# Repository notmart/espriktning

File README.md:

# espriktning bme280
ESP8266 based board replacement for Vindriktning with PM1006 and BME280 sensors

All started from Hypfer to send PM2.5 values to MQTT server

[https://github.com/Hypfer/esp8266-vindriktning-particle-sensor](https://github.com/Hypfer/esp8266-vindriktning-particle-sensor)

Then some custom PCB to fit inside the case, because adding some object in the case seems to modify PM2.5 readings.

[https://hackaday.io/project/181195-ikea-vindriktning-pcb](https://hackaday.io/project/181195-ikea-vindriktning-pcb)

But we need to read the PM2.5 values from the front of the device, not only a generic light!
So why not completely replacing IKEA PCB? there is the notmart ESPriktning project that still uses an ESP8266 board on a single completely new board

[https://github.com/notmart/espriktning](https://github.com/notmart/espriktning)

At this point, adding an additional sensor to measure temperature, humidity and pressure is simple using a small BME280 sensor. This fork adds MQTT data pushing if the BME280 is connected, and a display notification also for temperature.

Board inside:

PM2.5 local display:

Temperature local display:

## Board deployment

Use Arduino 1.8.0 onward

Add ESP8266 board (File -> Preferences -> Additional Boards Manager URLs)
* http://arduino.esp8266.com/stable/package_esp8266com_index.json

Add following libaries (Tools -> Library):
* 	WiFiMQTTManager Library 1.0.1-beta
* 	WiFiManager 2.0.11-beta
* 	PubSubClient 2.8.0
* 	BME280 3.0.0 by Tyler Glenn
* 	NeoPixelBus by Makuna 2.7.0

Add the board (Tools -> Board -> Boards Manager)
* 	esp8266 3.0.2
	
Choose a compatible board (Tools -> Board -> ESP8266 Boards (3.0.2) )
* 	Generic ESP8266 Module or LOLIN(WEMOS) D1 mini (clone) 

## User configuration

At the first start, the board enables an WiFi Access Point.
Join the WiFi network, that has name "ESPriktning" with no password.
Access with web browser the address:
>  http://192.168.4.1/ 

Here under the "Configure WiFi" page you can configure:
* SSID and WPA password of your WiFi network
* IP address and TCP port of your MQTT server
* A configurable topic prefix
* Optionally username and password for MQTT authentication
 
### Measurement to MQTT

The MQTT values will be pushed to the server on the following topics:
* PM2.5 in ug/m^3 ->   PREFIX/pm2_5
* temperature in °C ->   PREFIX/temp
* pressure in hPa ->   PREFIX/pres
* humidity in % ->   PREFIX/hum

Sample publish values:

```
err@elitedesk:~$ mosquitto_sub -v -h localhost -t '#'
esprikningstudio/pm2_5 11
esprikningstudio/temp 32.92
esprikningstudio/pres 980.68
esprikningstudio/hum 25.13
```

If BME280 is not found, temperature, pressure and humidity are not sent.

### Reset of settings

Can be accomplished:
1. From Arduino, under Tools -> Erase Flash -> All Flash Contents
2. Physically pressing the SW2 flash pins for more that 2 seconds
3. From Arduino serial connection

## Serial interface

Write "help" from serial monitor interface. Speed is 115200 baud.

```
help
Commands:
help                   Shows this help
reboot                 Reboots the device
printwifisettings      Prints SSID and password of the current wifi connection
connectwifi SSID pass  Attempts to connect to a new wifi network
testnumber  num        Tests the number and color animation with the given 0-99 number
printsettings          Prints all available settings
get config_key         Prints the value of the given config key
set config_key value   Sets the value of the given config key to the given value
factoryreset           Forgets wifi and other settings, starts as new
turning fan off
```

## Greetings

This project exists thankfully to:
<a href="http://avvoca.to.it/">DLx</a>
<a href="http://notmart.org/">notmart</a>

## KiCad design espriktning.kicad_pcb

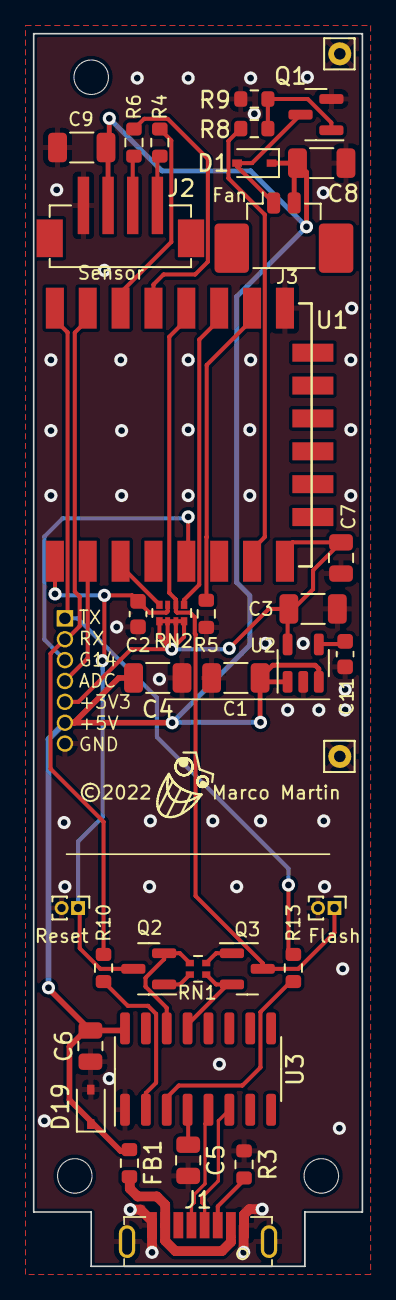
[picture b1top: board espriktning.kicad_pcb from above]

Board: 2 copper layers, 20.0 x 75.0 mm, 37 parts (0 on the bottom side), 31 nets.

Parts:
C1, C3, C4, C8, C9: 10u; C_1206_3216Metric
C2, C11: 470p; C_0603_1608Metric
C5, C6: 100n; C_0805_2012Metric
C7: 100u; C_0805_2012Metric
D1, D19: 1N4007; D_SOD-323
FB1: 60R; R_0603_1608Metric
J1: USB_C_Receptacle_USB2.0; usb-c-vertical-8
J2: Conn_Sensor; X1502WVS-04-9TSN
J3: Conn_Fan; Molex_PicoBlade_53398-0271_1x02-1MP_P1.25mm_Vertical
J4: Conn_01x08; PinSocket_1x07_P1.27mm_Vertical
J6, J7: Conn_01x01_Male; Pin_D0.7mm_L6.5mm_W1.8mm_FlatFork
Q1: 2N7002K; SOT-23
Q2, Q3: S8050; SOT-23
R3: 5.1k; R_0603_1608Metric
R4, R6, R10, R13: 470R; R_0603_1608Metric
R5, R9: 12k; R_0603_1608Metric
R8: 100; R_0603_1608Metric
RN1: 10k; R_Array_Convex_2x0402
RN2: 12k; R_Array_Convex_4x0402
SW1: Reset; PinHeader_1x02_P1.00mm_Vertical
SW2: Flash; PinHeader_1x02_P1.00mm_Vertical
U1: ESP-12F; ESP-12E_SMD
U2: SPX3819M5-L-3-3_SOT-23-5; SOT-23-5
U3: CH340C; SOIC-16_3.9x9.9mm_P1.27mm

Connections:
+3V3: C3.1, C7.1, J4.5, RN2.5 (R4.2), RN2.6 (R3.2), RN2.7 (R2.2), RN2.8 (R1.2), U1.8 (VCC), U2.5 (OUT)
+5V: C1.1, C4.1, C6.1, C8.1, C9.1, D1.1 (K), D19.1 (K), FB1.2, J2.2, J3.2, J4.6, U2.1 (IN), U2.3 (EN), U3.16 (VCC)
/D_N: J1.B7 (D-), U3.6 (UD-)
/D_P: J1.B6 (D+), U3.5 (UD+)
/VBUS: FB1.1, J1.A4 (VBUS)
ADC: J4.4, U1.2 (ADC)
GND: C1.2, C2.2, C3.2, C4.2, C5.2, C6.2, C7.2, C8.2, C9.2, C11.2, D19.2 (A), J1.A1 (GND), J1.S1 (SHIELD), J2.1, J4.7, J6.1, J7.1, Q1.2 (S), R3.1, R5.2, R9.2, SW1.2, SW2.2, U1.9 (GND), U2.2 (GND), U3.1 (GND)
GPIO0: Q3.3 (C), RN2.2 (R2.1), SW2.1, U1.12 (GPIO0)
GPIO2: RN2.1 (R1.1), U1.11 (GPIO2)
GPIO4: R6.2, U1.13 (GPIO4)
GPIO5: R4.2, U1.14 (GPIO5)
GPIO13: R8.2, U1.7 (GPIO13)
GPIO14: J4.3, U1.5 (GPIO14)
GPIO15: R5.1, U1.10 (GPIO15)
unnamed: C5.1, U3.4 (V3)
unnamed: C11.1, U2.4 (BP)
unnamed: D1.2 (A), J3.1, Q1.3 (D)
unnamed: J1.A5 (CC1), R3.2
unnamed: J2.3, R6.1
unnamed: J2.4, R4.1
unnamed: Q1.1 (G), R8.1, R9.1
unnamed: Q2.1 (B), RN1.2 (R1.2)
unnamed: Q2.2 (E), RN1.4 (R2.2), U3.14 (~RTS)
unnamed: Q3.1 (B), RN1.3 (R2.1)
unnamed: Q3.2 (E), RN1.1 (R1.1), U3.13 (~DTR)
unnamed: R10.2, U3.2 (TXD)
unnamed: R13.2, U3.3 (RXD)
unnamed: RN2.4 (R4.1), U1.3 (CH_PD)
RST: C2.1, Q2.3 (C), RN2.3 (R3.1), SW1.1, U1.1 (REST)
RX: J4.2, R10.1, U1.15 (RXD)
TX: J4.1, R13.1, U1.16 (TXD)

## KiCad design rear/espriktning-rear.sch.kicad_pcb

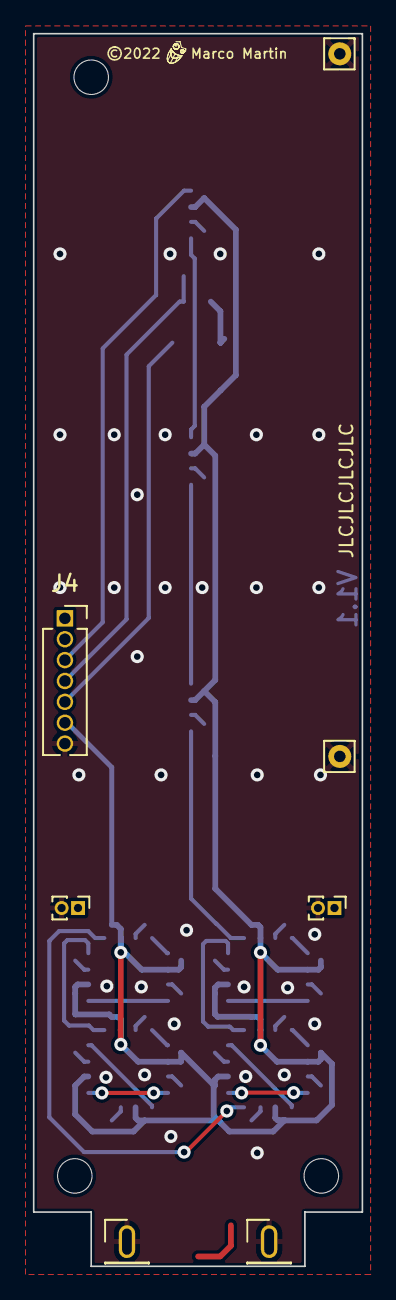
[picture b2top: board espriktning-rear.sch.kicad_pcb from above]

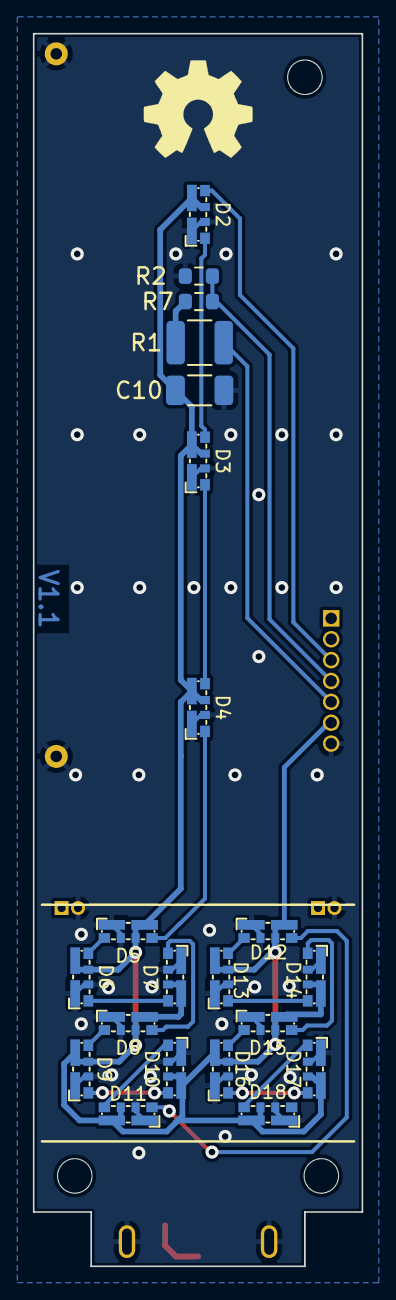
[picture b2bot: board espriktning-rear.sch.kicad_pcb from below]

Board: 2 copper layers, 20.0 x 75.0 mm, 26 parts (21 on the bottom side), 22 nets.

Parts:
C10: 10u; C_1206_3216Metric
D2, D3, D4, D5, D6, D7, D8, D9, D10, D11, D12, D13, D14, D15, D16, D17, D18: SK6812; SK6812D-EC3210R
J2, J3: Conn_01x01_Male; Pin_D0.7mm_L6.5mm_W1.8mm_FlatFork
J4: Conn_01x08; PinSocket_1x07_P1.27mm_Vertical
R1: GT36528; R_1210_3225Metric
R2, R7: 12k; R_0603_1608Metric
SW1: Reset; PinHeader_1x02_P1.00mm_Vertical
SW2: Flash; PinHeader_1x02_P1.00mm_Vertical

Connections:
+3V3: J4.5, R1.1
+5V: C10.1, D2.3 (VDD), D3.3 (VDD), D4.3 (VDD), D5.3 (VDD), D6.3 (VDD), D7.3 (VDD), D8.3 (VDD), D9.3 (VDD), D10.3 (VDD), D11.3 (VDD), D12.3 (VDD), D13.3 (VDD), D14.3 (VDD), D15.3 (VDD), D16.3 (VDD), D17.3 (VDD), D18.3 (VDD), J4.6
ADC: J4.4, R2.1, R7.2
GND: C10.2, D2.1 (VSS), D3.1 (VSS), D4.1 (VSS), D5.1 (VSS), D6.1 (VSS), D7.1 (VSS), D8.1 (VSS), D9.1 (VSS), D10.1 (VSS), D11.1 (VSS), D12.1 (VSS), D13.1 (VSS), D14.1 (VSS), D15.1 (VSS), D16.1 (VSS), D17.1 (VSS), D18.1 (VSS), J2.1, J3.1, J4.7, R2.2, SW1.2, SW2.2
GPIO14: D2.2 (DIN), J4.3
unnamed: D2.4 (DOUT), D3.2 (DIN)
unnamed: D3.4 (DOUT), D4.2 (DIN)
unnamed: D4.4 (DOUT), D5.2 (DIN)
unnamed: D5.4 (DOUT), D6.2 (DIN)
unnamed: D6.4 (DOUT), D7.2 (DIN)
unnamed: D7.4 (DOUT), D8.2 (DIN)
unnamed: D8.4 (DOUT), D9.2 (DIN)
unnamed: D9.4 (DOUT), D10.2 (DIN)
unnamed: D10.4 (DOUT), D11.2 (DIN)
unnamed: D11.4 (DOUT), D12.2 (DIN)
unnamed: D12.4 (DOUT), D13.2 (DIN)
unnamed: D13.4 (DOUT), D14.2 (DIN)
unnamed: D14.4 (DOUT), D15.2 (DIN)
unnamed: D15.4 (DOUT), D16.2 (DIN)
unnamed: D16.4 (DOUT), D17.2 (DIN)
unnamed: D17.4 (DOUT), D18.2 (DIN)
unnamed: R1.2, R7.1

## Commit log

2022-04-17 dd license
2022-04-17 remove zipped gerbers
2022-04-17 remove backups
2022-04-17 separate file for the rear
2022-05-05 relayout to actually fit
2022-05-05 update gerber
2022-05-05 add gerber
2022-05-18 Add the arduino sketch
2022-05-20 support animations
2022-05-20 fix blue
2022-05-23 every 2 minutes if night turn off the lights
2022-05-23 animation duration as variable
2022-05-24 better colors, show an help commandline
2022-05-26 Settings class, still not used
2022-05-27 manipulate the settings with the command line
2022-05-28 port WifiMQTTManager to Settings
2022-05-30 fix settings save/restore and colors
2022-05-31 add animation duration config value
2022-06-03 slightly more reliable wifi connection?
2022-07-02 wifi workaround
2022-08-17 fix usb power
2022-08-19 support for optional aht10
2022-08-19 topics for temp and humidity configurable
2022-08-19 little adjustment for temperature color
2022-08-26 arduino code for BME280, file reorganization, creating README.md
2022-08-26 wait for PM2.5 initial wrong values, fix temperature display, adding temperature compensation, fix MQTT attempt, README review
2022-08-26 README review
2022-08-28 fix MQTT blocking when connections goes down, better temperature approximations
2022-08-28 better temperature approximations
2022-08-28 Readme
2026-03-13 Better manage when the tem sensor is not attached
    also, watchdog and less insistent to connect to mqtt

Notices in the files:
espriktning.kicad_pcb:
©2022 Marco Martin
